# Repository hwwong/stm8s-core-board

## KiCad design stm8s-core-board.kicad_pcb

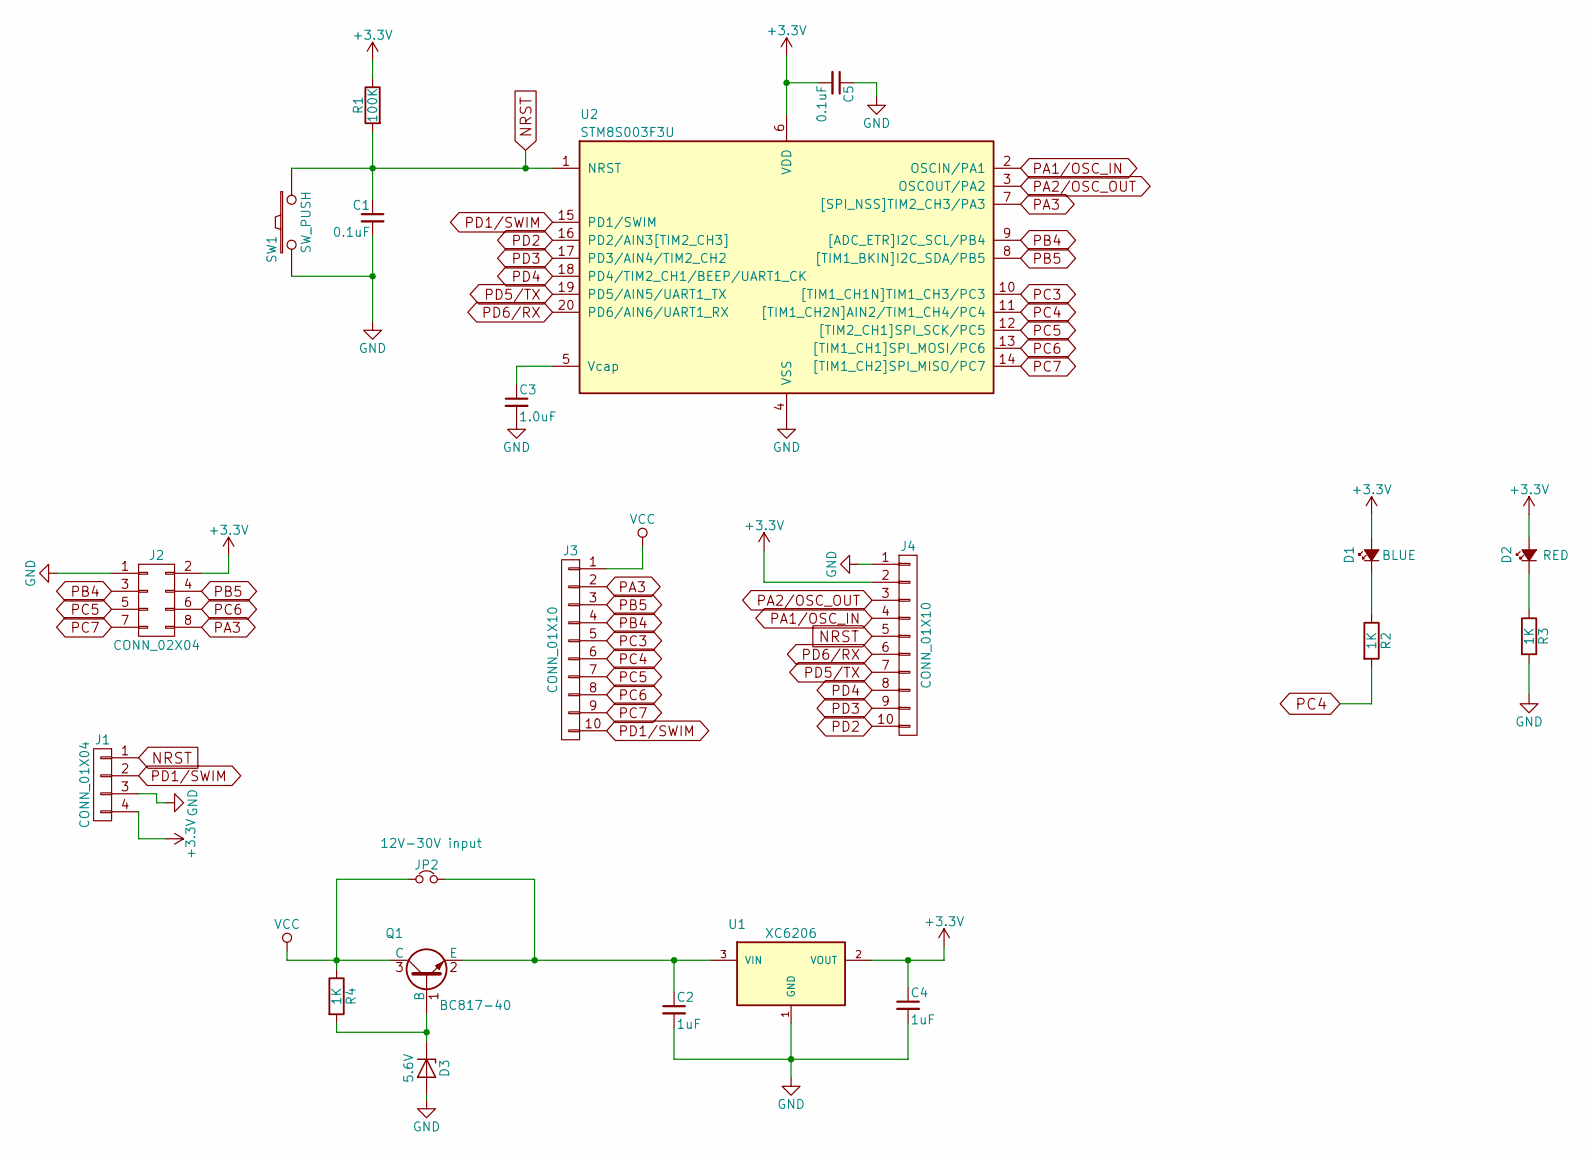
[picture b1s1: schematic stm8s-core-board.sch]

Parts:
C1, C5: 0.1uF; C_0603
C2, C4: 1uF; C_0603
C3: 1.0uF; C_0805
D1: BLUE; LED_0603
D2: RED; LED_0603
D3: 5.6V; SOD-80
J1: CONN_01X04; 1X04_LOCK
J2: CONN_02X04; 2X4
J3, J4: CONN_01X10; 1X10_LOCK_NS
JP2: 12V-30V input; SMT-JUMPER_2_NO_NO-SILK
Q1: BC817-40; SOT-23
R1: 100K; R_0603
R2, R3, R4: 1K; R_0603
SW1: SW_PUSH; SW_SPST_B3U-1000P
U1: XC6206; SOT-23
U2: STM8S003F3U; UQFN-16_3x3mm_Pitch0.5mm

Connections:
+3V3: C4.1, C5.2, D1.2 (A), D2.2 (A), J1.4, J2.2, J4.2, R1.1, U1.2 (VOUT), U2.6 (VDD)
GND: C1.2, C2.2, C3.2, C4.2, C5.1, D3.2 (A), J1.3, J2.1, J4.1, R3.2, SW1.2, U1.1 (GND), U2.4 (VSS)
NRST: C1.1, J1.1, J4.5, R1.2, SW1.1, U2.1 (NRST)
unnamed: C2.1, JP2.2, Q1.2 (E), U1.3 (VIN)
unnamed: C3.1, U2.5 (Vcap)
unnamed: D1.1 (K), R2.1
unnamed: D2.1 (K), R3.1
unnamed: D3.1 (K), Q1.1 (B), R4.2
PA1/OSC_IN: J4.4, U2.2 (OSCIN/PA1)
PA2/OSC_OUT: J4.3, U2.3 (OSCOUT/PA2)
PA3: J2.8, J3.2, U2.7 ([SPI_NSS]TIM2_CH3/PA3)
PB4: J2.3, J3.4, U2.9 ([ADC_ETR]I2C_SCL/PB4)
PB5: J2.4, J3.3, U2.8 ([TIM1_BKIN]I2C_SDA/PB5)
PC3: J3.5, U2.10 ([TIM1_CH1N]TIM1_CH3/PC3)
PC4: J3.6, R2.2, U2.11 ([TIM1_CH2N]AIN2/TIM1_CH4/PC4)
PC5: J2.5, J3.7, U2.12 ([TIM2_CH1]SPI_SCK/PC5)
PC6: J2.6, J3.8, U2.13 ([TIM1_CH1]SPI_MOSI/PC6)
PC7: J2.7, J3.9, U2.14 ([TIM1_CH2]SPI_MISO/PC7)
PD1/SWIM: J1.2, J3.10, U2.15 (PD1/SWIM)
PD2: J4.10, U2.16 (PD2/AIN3[TIM2_CH3])
PD3: J4.9, U2.17 (PD3/AIN4/TIM2_CH2)
PD4: J4.8, U2.18 (PD4/TIM2_CH1/BEEP/UART1_CK)
PD5/TX: J4.7, U2.19 (PD5/AIN5/UART1_TX)
PD6/RX: J4.6, U2.20 (PD6/AIN6/UART1_RX)
VCC: J3.1, JP2.1, Q1.3 (C), R4.1

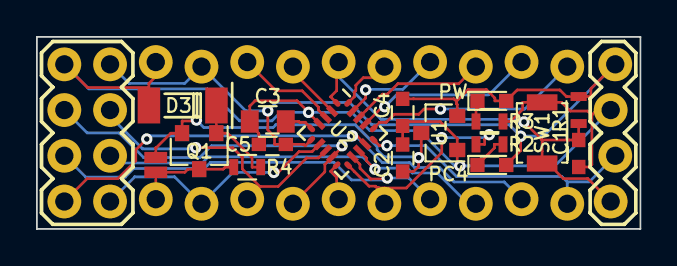
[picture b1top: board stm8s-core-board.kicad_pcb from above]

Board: 2 copper layers, 33.5 x 10.7 mm, 21 parts (0 on the bottom side), 25 nets.

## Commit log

2018-10-21 forgot commit for long time. don't know what changed
